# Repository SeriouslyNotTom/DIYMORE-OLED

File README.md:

<h1>What is This?</h1>
<p>this is a backpack for the diymore 2.42" OLED SSD1309 display</p>
<p>it allows for the display + I/O to be connected via a singular Ribbon Cable</p>

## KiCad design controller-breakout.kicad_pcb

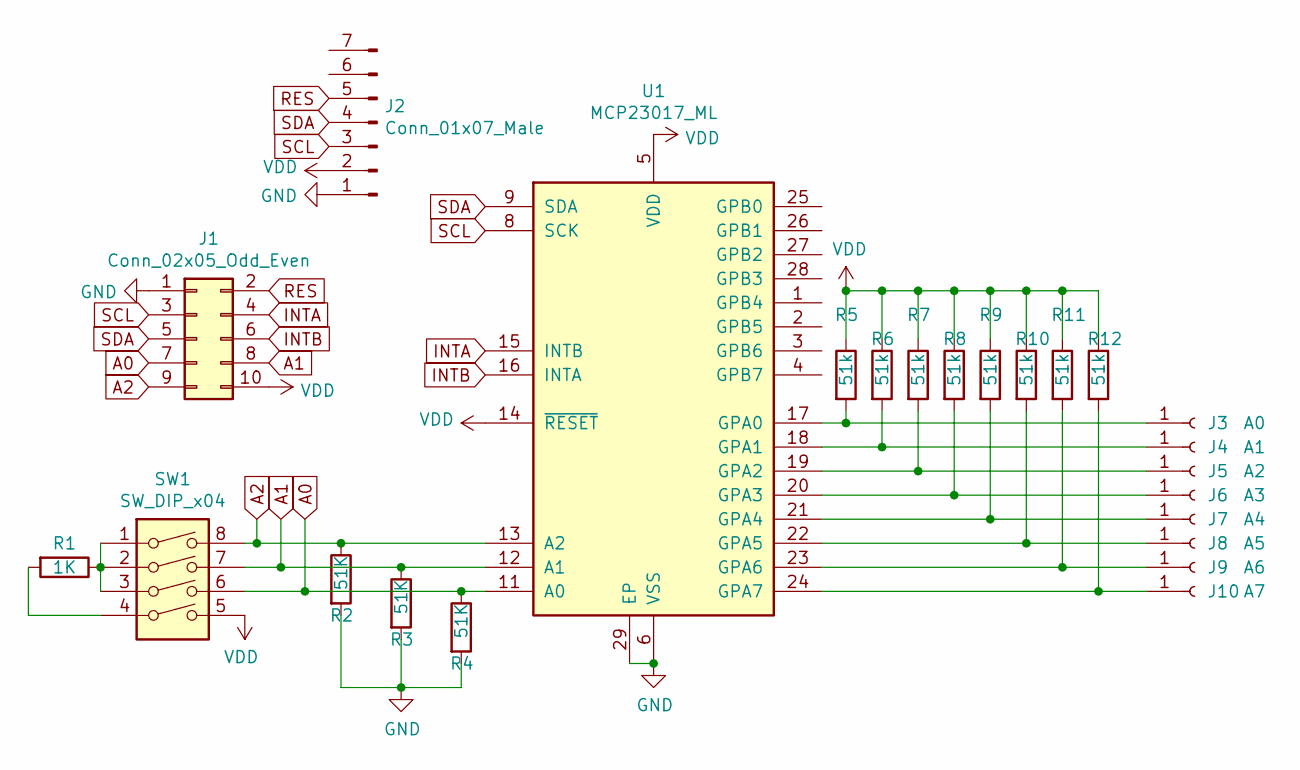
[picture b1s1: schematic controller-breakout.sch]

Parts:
J1: Conn_02x05_Odd_Even; PinHeader_2x05_P2.54mm_Vertical_SMD
J2: Conn_01x07_Male; oled_footprint
J3: A0; Solder_Connector
J4: A1; Solder_Connector
J5: A2; Solder_Connector
J6: A3; Solder_Connector
J7: A4; Solder_Connector
J8: A5; Solder_Connector
J9: A6; Solder_Connector
J10: A7; Solder_Connector
R1: 1K; R_0805_2012Metric
R2, R3, R4: 51K; R_0805_2012Metric
R5, R6, R7, R8, R9, R10, R11, R12: 51k; R_0805_2012Metric
SW1: SW_DIP_x04; SW_DIP_SPSTx04_Slide_6.7x11.72mm_W8.61mm_P2.54mm_LowProfile
U1: MCP23017_ML; QFN-28-1EP_6x6mm_P0.65mm_EP4.25x4.25mm

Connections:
A0: J1.7, R4.1, SW1.6, U1.11 (A0)
A1: J1.8, R3.1, SW1.7, U1.12 (A1)
A2: J1.9, R2.1, SW1.8, U1.13 (A2)
GND: J1.1, J2.1, R2.2, R3.2, R4.2, U1.6 (VSS), U1.29 (EP)
INTA: J1.4, U1.15 (INTB)
INTB: J1.6, U1.16 (INTA)
unnamed: J3.1, R5.2, U1.17 (GPA0)
unnamed: J4.1, R6.2, U1.18 (GPA1)
unnamed: J5.1, R7.2, U1.19 (GPA2)
unnamed: J6.1, R8.2, U1.20 (GPA3)
unnamed: J7.1, R9.2, U1.21 (GPA4)
unnamed: J8.1, R10.2, U1.22 (GPA5)
unnamed: J9.1, R11.2, U1.23 (GPA6)
unnamed: J10.1, R12.2, U1.24 (GPA7)
unnamed: R1.1, SW1.1, SW1.2, SW1.3
unnamed: R1.2, SW1.4
RES: J1.2, J2.5
SCL: J1.3, J2.3, U1.8 (SCK)
SDA: J1.5, J2.4, U1.9 (SDA)
VDD: J1.10, J2.2, R5.1, R6.1, R7.1, R8.1, R9.1, R10.1, R11.1, R12.1, SW1.5, U1.5 (VDD), U1.14 (~RESET~)

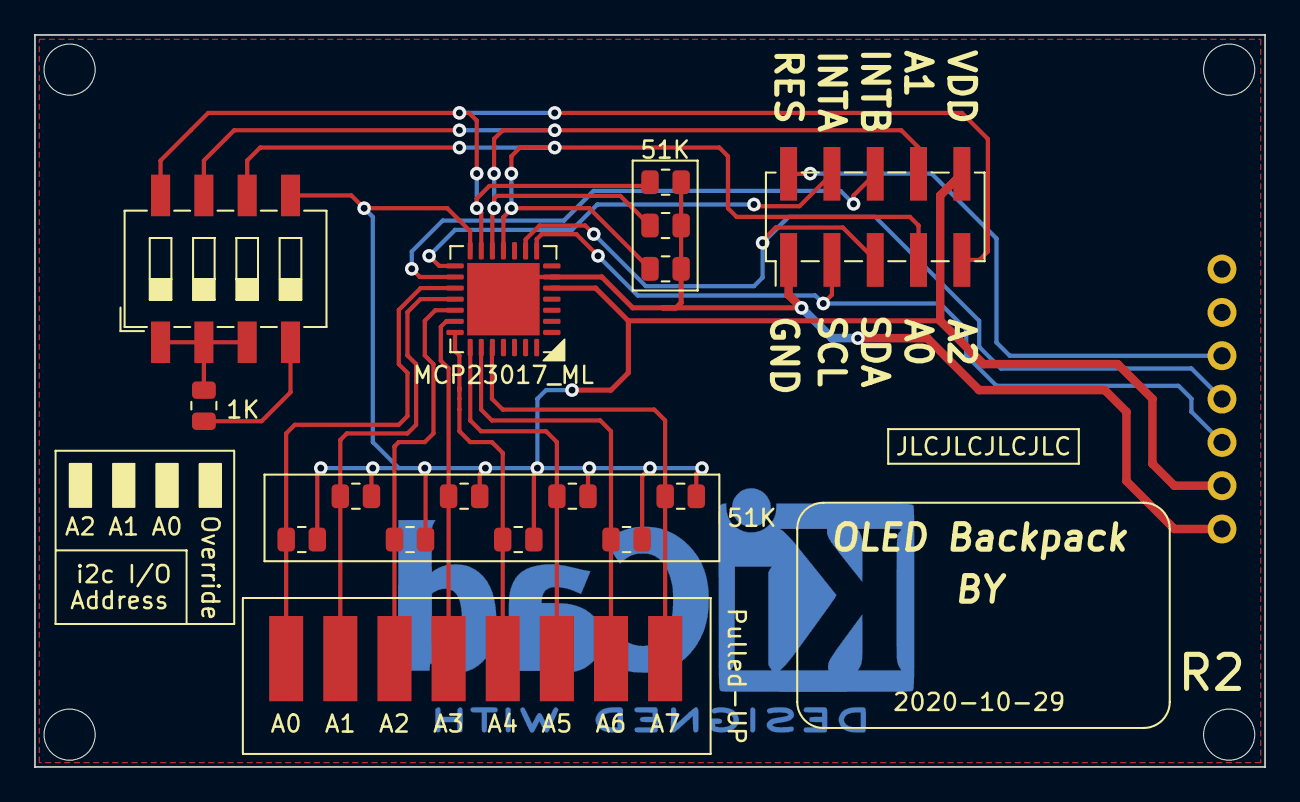
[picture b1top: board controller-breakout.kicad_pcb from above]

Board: 2 copper layers, 72.1 x 42.9 mm, 24 parts (0 on the bottom side), 20 nets.

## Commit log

2021-01-06 init files
